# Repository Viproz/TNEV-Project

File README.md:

# TNEV-Project

Pour installer l'ide : http://download.netbeans.org/netbeans/8.0.2/final/bundles/netbeans-8.0.2-cpp-windows.exe

L'installer puis installer le plugin Arduino : http://plugins.netbeans.org/plugin/46054/arduino (http://plugins.netbeans.org/download/plugin/2774)

Suivre le tuto ici : http://arduino-netbeans.googlecode.com/files/Install.pdf

Et voilà !

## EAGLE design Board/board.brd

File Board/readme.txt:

SND = SouND sensor
BUZ = BUZzer
SRV = SeRVo-motor
MOT = MOTor
SW = SWitch
WHL = WHeeL (photosensors)
PHS = PHotoSensors
ALIM = ALIMentation

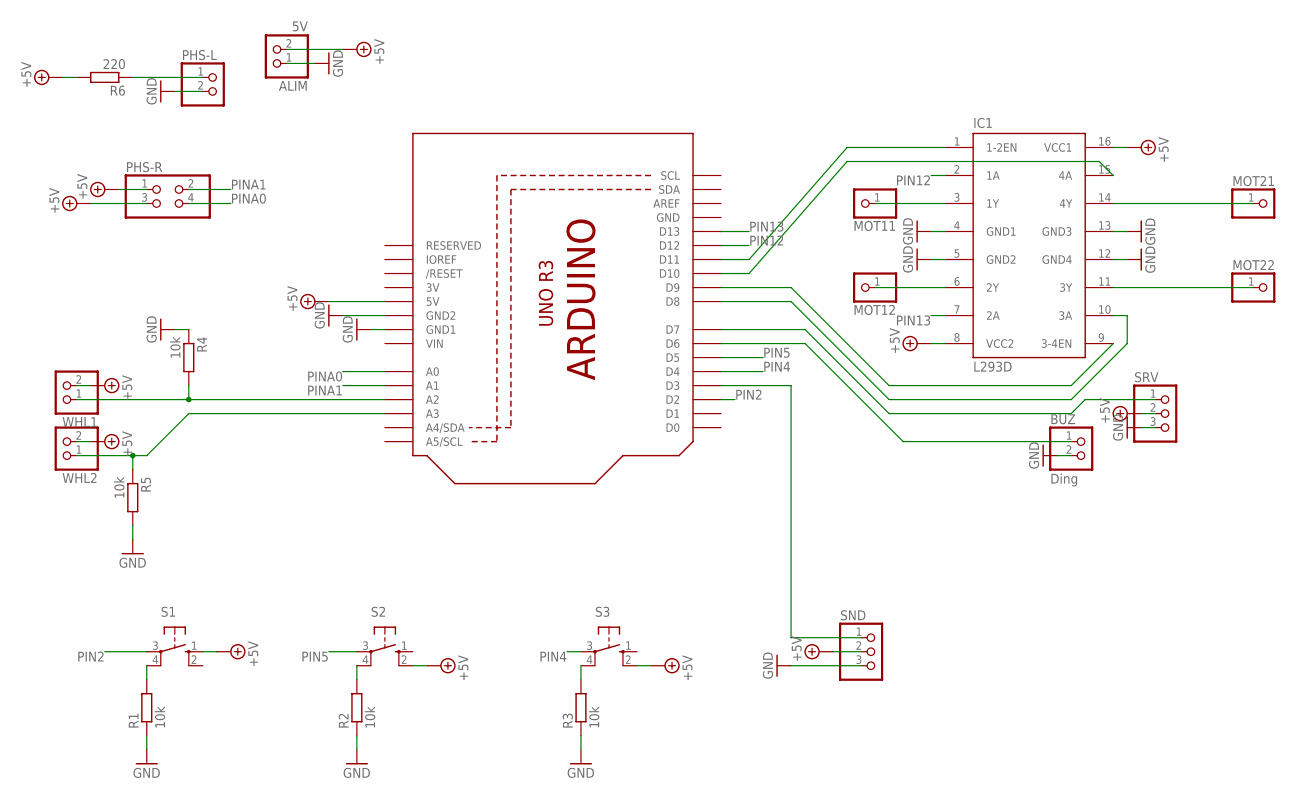
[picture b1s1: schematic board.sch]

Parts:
ALIM: 5V; 1X02
BUZ: Ding; 1X02
IC1: L293D; DIL16
MOT11, MOT12, MOT21, MOT22: PINHD-1X1; 1X01
PHS-L: PINHD-1X2; 1X02
PHS-R: PINHD-2X2; 2X02
R1, R2, R3, R4, R5: 10k; R1206
R6: 220; R1206
S1, S2, S3: 10-XX; B3F-10XX
SND: PINHD-1X3; 1X03
SRV: PINHD-1X3/90; 1X03/90
U1: ARDUINOR3-BPLACE
WHL1, WHL2: PINHD-1X2; 1X02

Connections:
3V: U1.3V
+5V: ALIM.2, IC1.8 (VCC2), IC1.16 (VCC1), PHS-R.1, PHS-R.3, R6.2, S1.1 (S), S2.2 (S1), S3.2 (S1), SND.2, SRV.2, U1.5V, WHL1.2, WHL2.2
GND: ALIM.1, BUZ.2, IC1.4 (GND1), IC1.5 (GND2), IC1.12 (GND4), IC1.13 (GND3), PHS-L.2, R1.1, R2.1, R3.1, R4.1, R5.2, SND.3, SRV.3, U1.GND, U1.GND1, U1.GND2
unnamed: IC1.3 (1Y), MOT11.1
unnamed: IC1.6 (2Y), MOT12.1
unnamed: IC1.14 (4Y), MOT21.1
unnamed: IC1.11 (3Y), MOT22.1
unnamed: IC1.15 (4A), U1.D10
unnamed: IC1.9 (3-4EN), U1.D9
unnamed: IC1.10 (3A), U1.D8
unnamed: IC1.1 (1-2EN), U1.D11
unnamed: R4.2, U1.A2, WHL1.1
unnamed: PHS-L.1, R6.1
unnamed: R5.1, U1.A3, WHL2.1
unnamed: SRV.1, U1.D7
unnamed: BUZ.1, U1.D6
unnamed: R2.2, S2.4 (P1)
unnamed: R3.2, S3.4 (P1)
unnamed: R1.2, S1.4 (P1)
unnamed: SND.1, U1.D3
PIN2: S1.3, U1.D2
PIN4: S3.3, U1.D4
PIN5: S2.3, U1.D5
PIN12: IC1.2 (1A), U1.D12
PIN13: IC1.7 (2A), U1.D13
PINA0: PHS-R.4, U1.A0
PINA1: PHS-R.2, U1.A1
VIN: U1.VIN

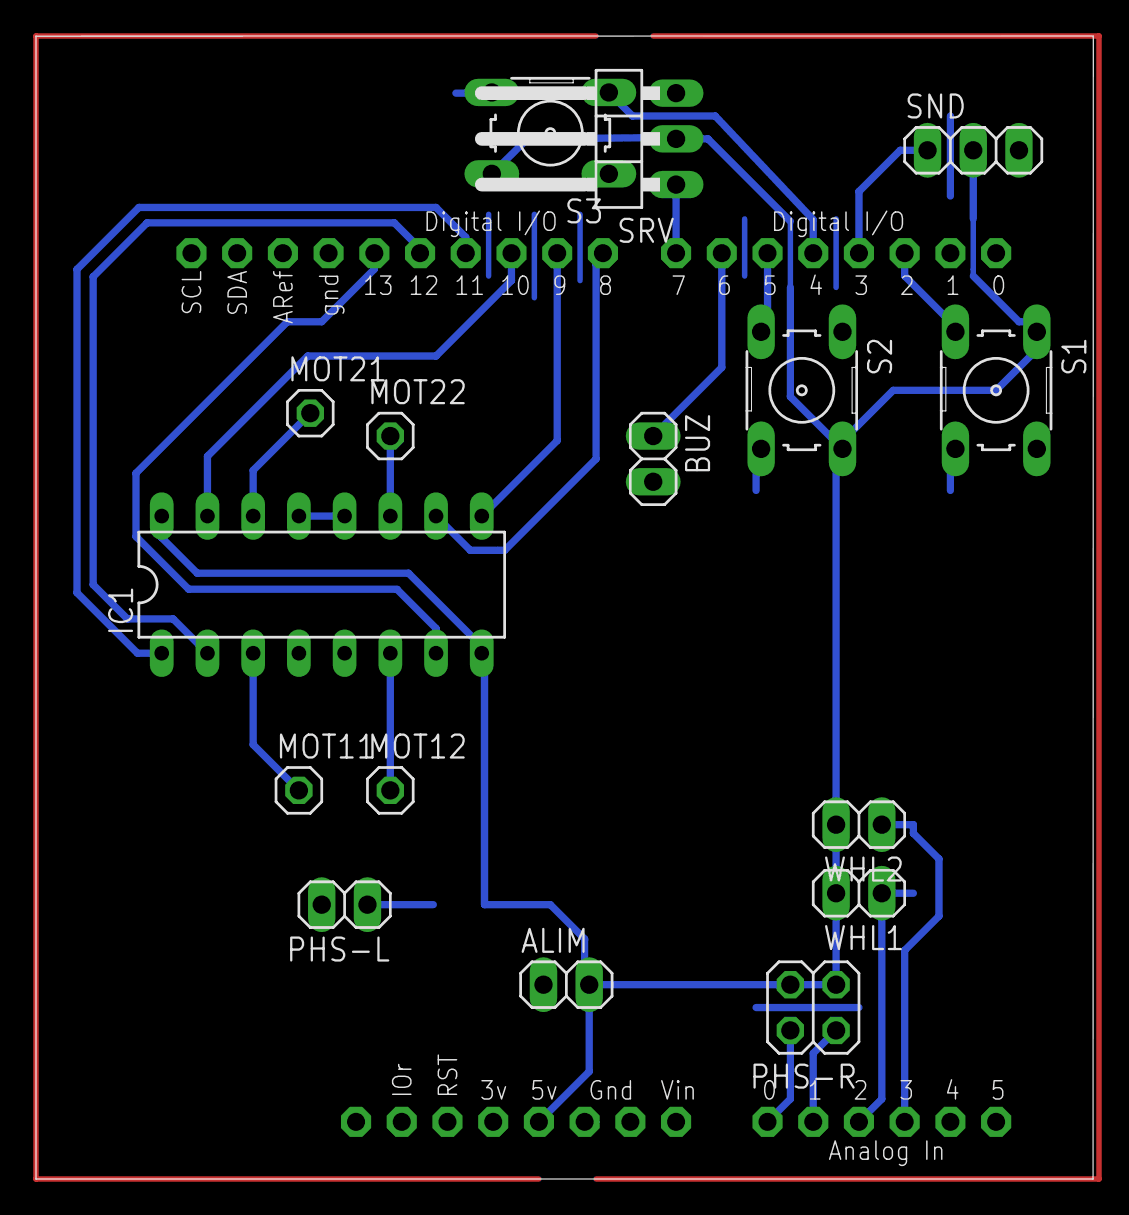
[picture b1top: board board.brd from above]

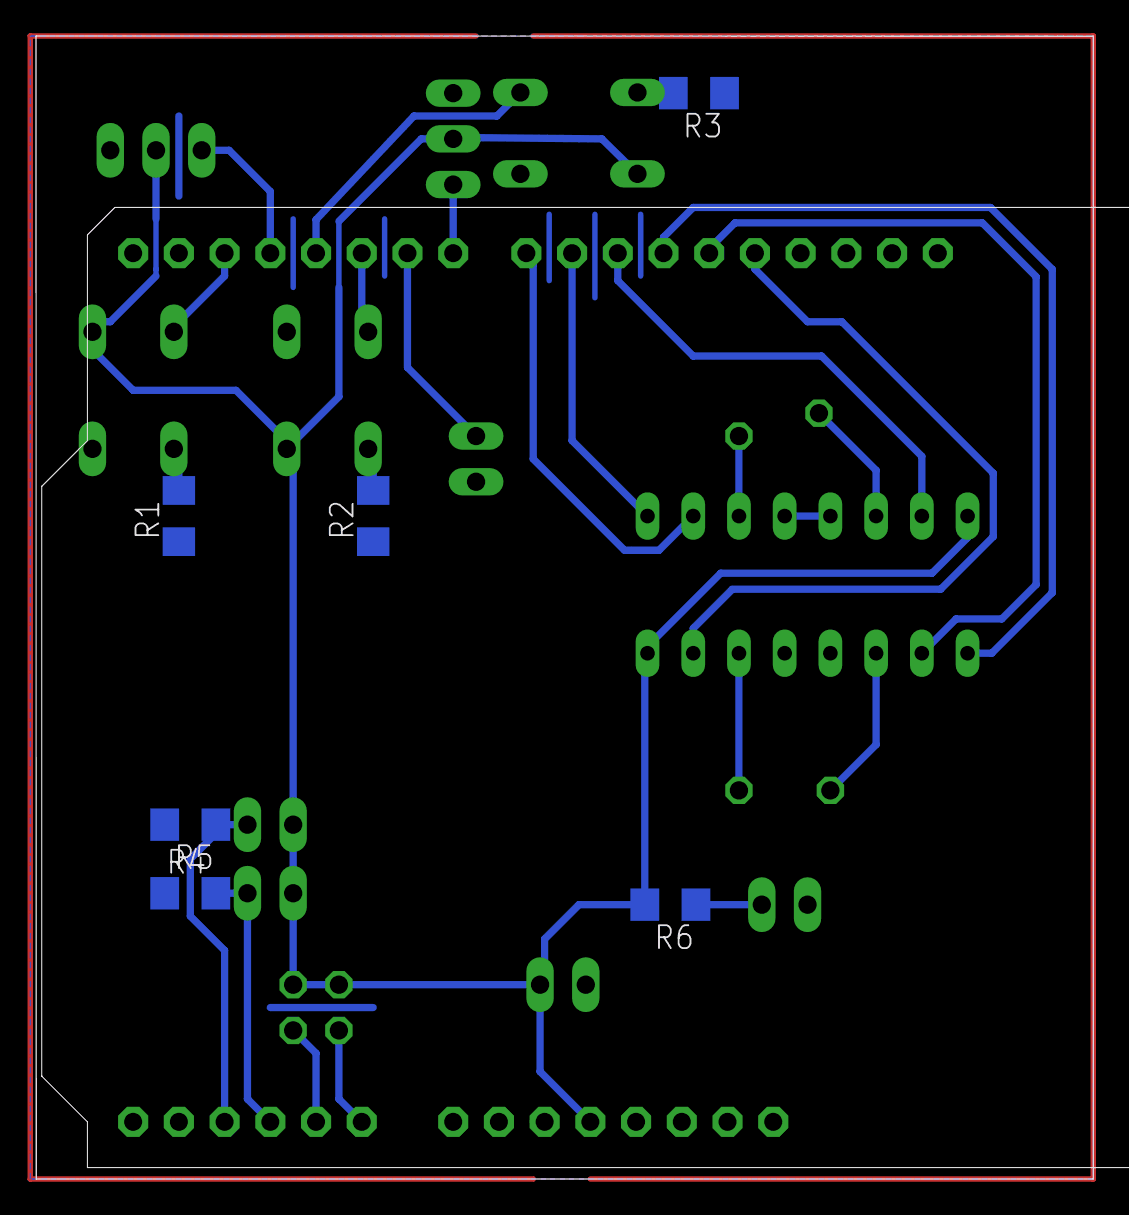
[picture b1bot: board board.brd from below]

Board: 2 copper layers, 58.7 x 63.5 mm, 23 parts (6 on the bottom side), 26 nets.

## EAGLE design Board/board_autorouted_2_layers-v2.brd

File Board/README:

The file tnev.cam contains all the params needed to generate the file for the printer

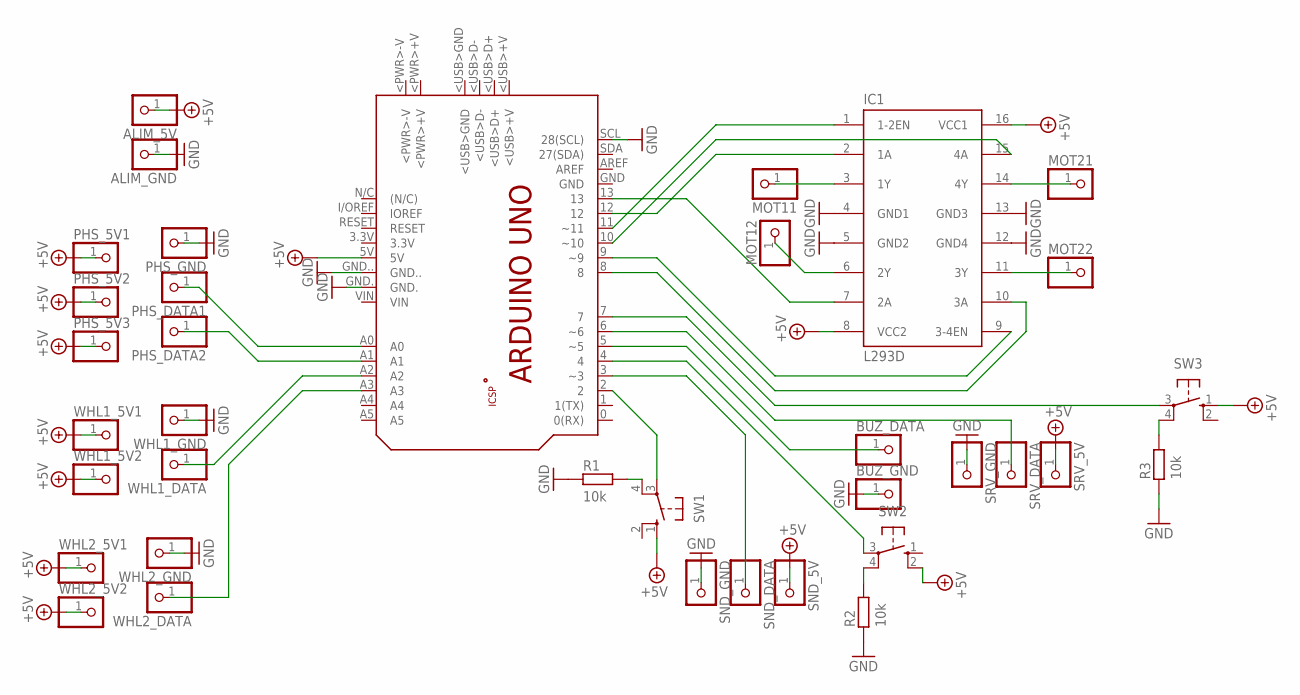
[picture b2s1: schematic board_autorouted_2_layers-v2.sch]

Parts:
ALIM_5V: PINHD-1X1; 1X01
ALIM_GND: PINHD-1X1; 1X01
BUZ_DATA: PINHD-1X1; 1X01
BUZ_GND: PINHD-1X1; 1X01
IC1: L293D; DIL16
MOT11, MOT12, MOT21, MOT22: PINHD-1X1; 1X01
PCB1: ARDUINO_UNO
PHS_5V1, PHS_5V2, PHS_5V3: PINHD-1X1; 1X01
PHS_DATA1, PHS_DATA2: PINHD-1X1; 1X01
PHS_GND: PINHD-1X1; 1X01
R1, R2, R3: 10k; R0603
SND_5V: PINHD-1X1; 1X01
SND_DATA: PINHD-1X1; 1X01
SND_GND: PINHD-1X1; 1X01
SRV_5V: PINHD-1X1; 1X01
SRV_DATA: PINHD-1X1; 1X01
SRV_GND: PINHD-1X1; 1X01
SW1, SW2, SW3: 40-XX; B3F-40XX
WHL1_5V1, WHL1_5V2, WHL1_DATA, WHL1_GND, WHL2_5V1, WHL2_5V2, WHL2_DATA, WHL2_GND: PINHD-1X1; 1X01

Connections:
+5V: ALIM_5V.1, IC1.8 (VCC2), IC1.16 (VCC1), PCB1.5V, PHS_5V1.1, PHS_5V2.1, PHS_5V3.1, SND_5V.1, SRV_5V.1, SW1.1 (S), SW2.2 (S1), SW3.1 (S), WHL1_5V1.1, WHL1_5V2.1, WHL2_5V1.1, WHL2_5V2.1
GND: ALIM_GND.1, BUZ_GND.1, IC1.4 (GND1), IC1.5 (GND2), IC1.12 (GND4), IC1.13 (GND3), PCB1.GND., PCB1.GND.., PCB1.SCL (28(SCL)), PHS_GND.1, R1.1, R2.1, R3.1, SND_GND.1, SRV_GND.1, WHL1_GND.1, WHL2_GND.1
unnamed: IC1.3 (1Y), MOT11.1
unnamed: IC1.6 (2Y), MOT12.1
unnamed: IC1.14 (4Y), MOT21.1
unnamed: IC1.11 (3Y), MOT22.1
unnamed: IC1.2 (1A), PCB1.12
unnamed: IC1.7 (2A), PCB1.13
unnamed: IC1.15 (4A), PCB1.10 (~10)
unnamed: IC1.9 (3-4EN), PCB1.9 (~9)
unnamed: IC1.10 (3A), PCB1.8
unnamed: IC1.1 (1-2EN), PCB1.11 (~11)
unnamed: PCB1.A1, PHS_DATA2.1
unnamed: PCB1.A0, PHS_DATA1.1
unnamed: PCB1.A3, WHL2_DATA.1
unnamed: PCB1.6 (~6), SRV_DATA.1
unnamed: PCB1.3 (~3), SND_DATA.1
unnamed: BUZ_DATA.1, PCB1.5 (~5)
unnamed: PCB1.7, SW3.3
unnamed: R3.2, SW3.4 (P1)
unnamed: PCB1.4, SW2.3
unnamed: R2.2, SW2.4 (P1)
unnamed: R1.2, SW1.4 (P1)
unnamed: PCB1.A2, WHL1_DATA.1
unnamed: PCB1.2, SW1.3

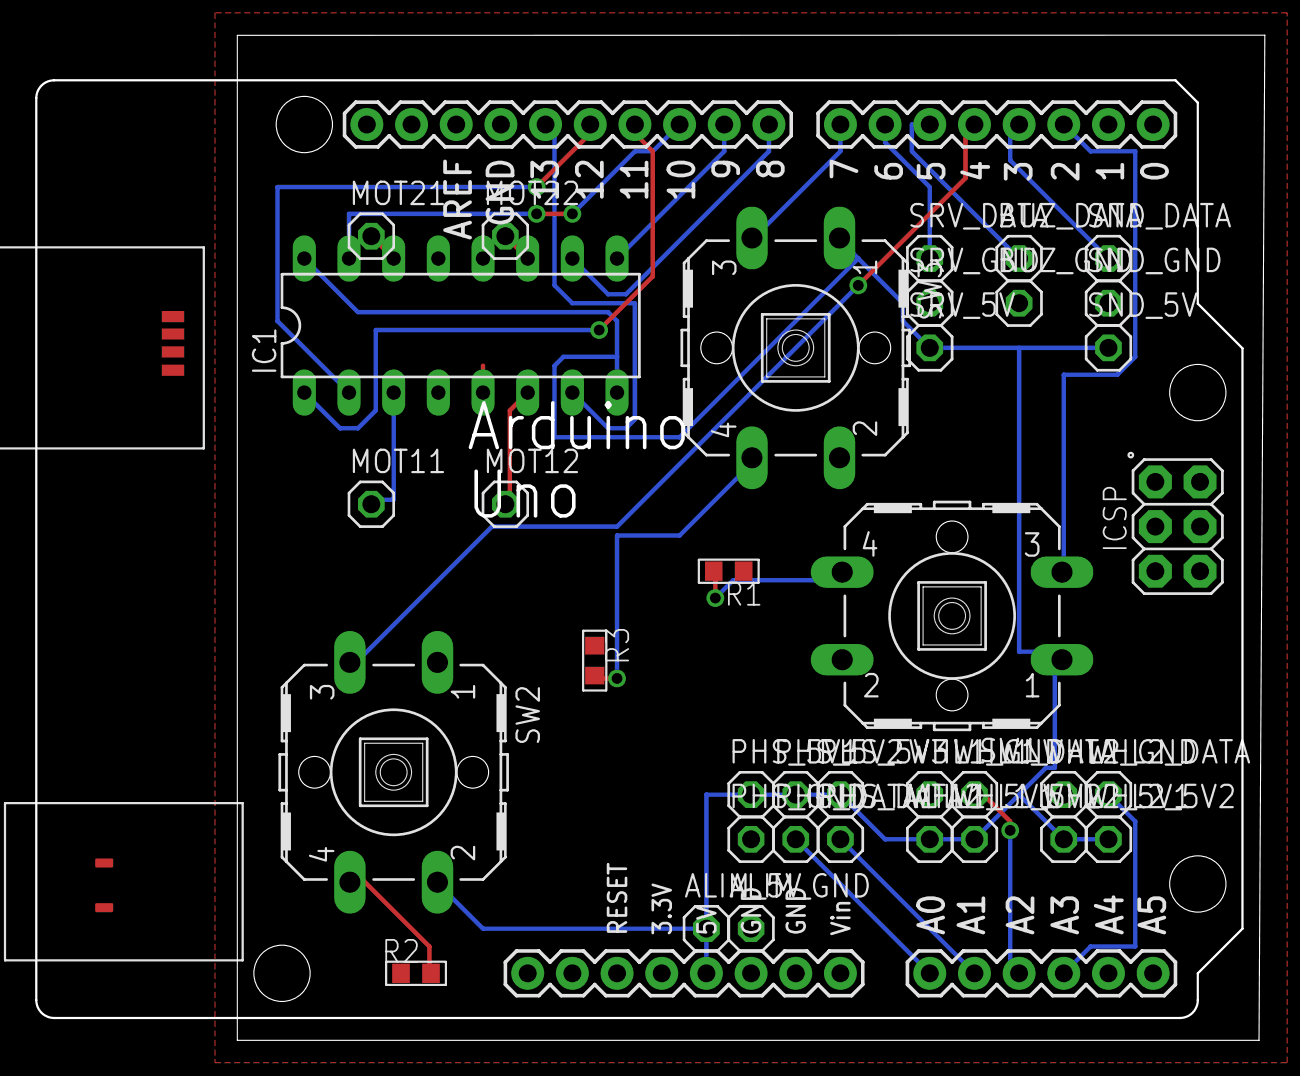
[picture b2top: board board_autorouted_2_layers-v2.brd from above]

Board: 2 copper layers, 69.8 x 57.0 mm, 36 parts (0 on the bottom side), 25 nets.

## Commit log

2015-04-08 Readme
2015-04-14 Little name fix
2015-04-22 Added Motor object
2015-04-22 Added MotorCarriage Object
2015-04-22 Big cleanup and functionnal main
2015-05-05 Typos
2015-05-17 Added MotorSensor and calibration
2015-05-17 Removed durp
2015-05-17 minor change
2015-05-17 removed netbeans project files
2015-05-17 moved in src
2015-05-17 Added speed calibration, turn implementation and goDistance Added structure for Ultrasonic sensor
2015-05-19 Added documentation
2015-05-21 added board stuff
2015-05-27 various stuff and board
2015-05-27 Eagle : Switches connected, useless backups deleted
    - Connected the switches left unconnected last time
    - Optimized the schematics
    - Removed the now useless backups & libraries - only kept the 3 most
    recent versions.
2015-05-27 Eagle : Added thumbwheels
2015-05-27 Finished, and autorouted everything on 2 layers.
2015-05-27 Optimization & 1-layer version
    - Made the schematics easier to read
    - Replaced blocks with individual pins - easier to know what is what
    once finished
    - Optimized for a single layer (90.7% success)
    - Some other minor things I forgot.
2015-05-31 Updated boad
2015-05-31 Board cleanup
2015-05-31 Fixed Logger
2015-05-31 Added Button class Updated MotorSensor for the new system.
2015-05-31 Fixed Servo Various corrections main.cpp cleanup
2015-06-01 Board preparation
2015-06-01 Board README
2015-06-01 Small changes
2015-06-01 Re-gen
2015-06-03 Added UltrasonicSensor func Fixed and tweaked vales for calibration
2015-06-04 stuffs
2015-06-08 Unfinished stuff
2015-06-08 added netbeans files
2015-06-08 fixed netbeans data
2015-06-08 removed private folder
2015-06-16 Final program
